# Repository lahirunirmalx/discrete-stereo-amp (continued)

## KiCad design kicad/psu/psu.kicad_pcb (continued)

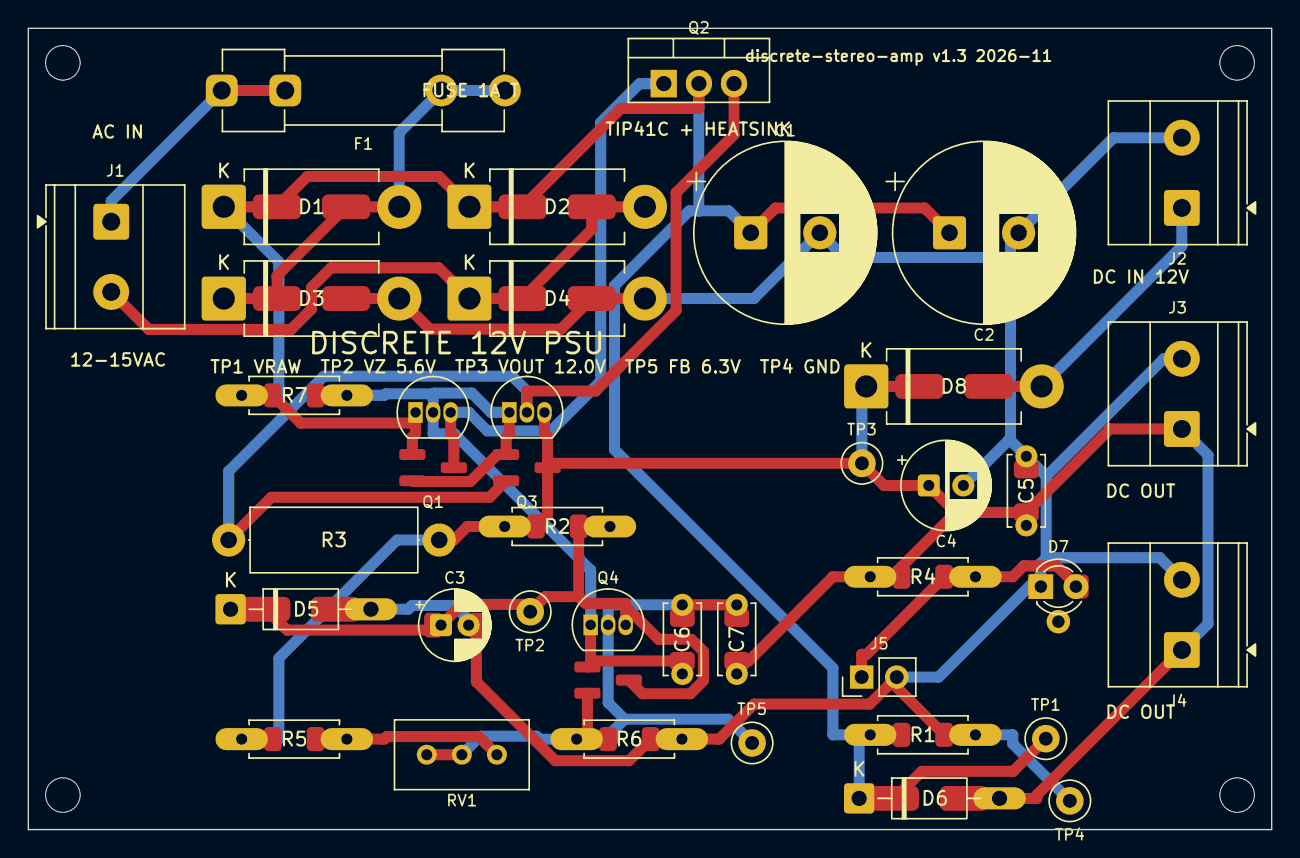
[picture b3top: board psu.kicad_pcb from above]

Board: 2 copper layers, 90.0 x 58.0 mm, 42 parts (0 on the bottom side), 14 nets.

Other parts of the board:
H1, H2, H3, H4: M2.5; Hole_2.5mm

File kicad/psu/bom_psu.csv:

board,qty,refs,value,through_hole,smd_alternative,tolerance_rating,substitutes,matching_note
psu,1,C5,100n,ceramic disc 5 mm,1206,100 nF X7R,100n,
psu,1,C7,100n,ceramic disc 5 mm,1206,"100 nF X7R, 50 V",100n,Feeds fast output steps to the error amplifier.
psu,1,C3,10u,electrolytic 5 mm radial,1206 MLCC,"10 uF, 16 V",4.7u to 47u,Reference filter across the 5.6 V zener.
psu,2,C1 C2,2200u,CP_Radial_D13.0mm_P5.00mm,,"2200 uF, 25 V (35 V if the transformer is 15 VAC)",2200u to 4700u,"Reservoir: raw rail peaks at 21 V no-load from 15 VAC, 23 V at mains +10 percent."
psu,1,C4,220u,CP_Radial_D6.3mm_P2.50mm,,"220 uF, 16 V",100u to 470u,
psu,1,C6,47n,ceramic disc 5 mm,1206,"47 nF X7R or film, 50 V",22n to 100n,"Loop compensation (Q4 collector to base). 22n is faster, 100n slower; all three are stable."
psu,1,D6,1N4007,DO-41,SMA,"1 A, 100 V or more",1N4007 (fitted); 1N4004; UF4007; SMA S1M,Reverse protection of the pass transistor.
psu,4,D1 D2 D3 D4,1N5401,DO-201AD,"SMA (3 A part, e.g. S3M)","3 A, 100 V or more","1N5401 (fitted); 1N5402 / 1N5404 / 1N5408 (same package, higher voltage); SB540 Schottky (less drop, runs cooler); S3M in SMA",All four the same type.
psu,1,D5,5.6V,DO-41,SMA,"5.6 V, 0.5 W, 5 percent",1N5232B (fitted); BZX55C5V6; BZX79C5V6; BZX85C5V6 (1 W); 1N4734A,"Reference. 5.6 V has near-zero tempco and its +2 mV/C cancels Q4's -2 mV/C Vbe; 5.1 V or 6.2 V also work, the trimmer absorbs the difference."
psu,1,D7,LED,3 mm LED (or two small diodes via the middle hole M),1206 LED,"3 mm LED, any colour",any 3 mm or 5 mm LED,"Fit D7 here OR D1 on the volume board, not both."
psu,1,D8,SB540,DO-201AD,"SMA (3 A part, e.g. S3M)","5 A Schottky, 40 V",SB540 (fitted); 1N5822 (3 A); SR540; MBR540; SS54 in SMA,"DC-in path, 0.4 V drop."
psu,1,F1,1.6A T 5x20,Fuseholder_Clip-5x20mm_Littelfuse_100_Inline_P20.50x4.60mm_D1.30mm_Horizontal,,1.6 A slow-blow (T) 5x20 mm + 2 clips,1.6 A T (fitted); 1.25 A T with a 12 VAC transformer; 2 A T only with a larger heatsink on Q2,"On the transformer secondary. Sized for the RMS secondary current (1.5 A at 0.8 A DC), and small enough that the 3.7 A of a clamped short opens it in seconds."
psu,1,J1,AC IN 12-15V,"TerminalBlock_Phoenix_MKDS-1,5-2-5.08_1x02_P5.08mm_Horizontal",,5.08 mm screw terminal,Phoenix MKDS 1.5/2; any 5.08 mm 2-pin block,
psu,1,J2,DC IN 12V,"TerminalBlock_Phoenix_MKDS-1,5-2-5.08_1x02_P5.08mm_Horizontal",,5.08 mm screw terminal,Phoenix MKDS 1.5/2; any 5.08 mm 2-pin block,
psu,1,J3,DC OUT 1,"TerminalBlock_Phoenix_MKDS-1,5-2-5.08_1x02_P5.08mm_Horizontal",,5.08 mm screw terminal,Phoenix MKDS 1.5/2; any 5.08 mm 2-pin block,
psu,1,J4,DC OUT 2,"TerminalBlock_Phoenix_MKDS-1,5-2-5.08_1x02_P5.08mm_Horizontal",,5.08 mm screw terminal,Phoenix MKDS 1.5/2; any 5.08 mm 2-pin block,
psu,1,J5,LED REMOTE,PinHeader_1x02_P2.54mm_Vertical,,"5 percent / 20 percent, standard",,
psu,3,Q1 Q3 Q4,BC547,TO-92,SOT-23 (2-layer board only),hFE 200-450,BC547B/C (fitted); BC548B/C; BC549C or BC550C (lower noise); BC337-25 (800 mA); 2N3904 or PN2222A only turned 180 deg (E-B-C pinout),"Driver (Q1), clamp (Q3) and error amplifier (Q4). No matching."
psu,1,Q2,TIP41C,TO-220-3_Vertical,,"6 A, 100 V, TO-220 on a heatsink","TIP41C (fitted, B-C-E); TIP31C (3 A); BD243C; MJE3055T; TIP41A/B (lower voltage grade is fine at 20 V). All B-C-E: this position has no jumper block",Pass transistor. Dissipates up to 4.9 W: heatsink of 10 C/W or better.
psu,1,R3,0.33 2W,R_Axial_DIN0414_L11.9mm_D4.5mm_P15.24mm_Horizontal,,"0.33 ohm, 3 W, 5 percent",0.33R 2-3 W; 0.47R gives a 1.4 A clamp; 0.22R gives 3 A,Clamp current = 0.65 V / R3.
psu,1,R6,10k,axial 1/4 W,1206,"10k, 1 percent, 1/4 W",10k,Bottom of the output divider. FB = 6.3 V (zener + Vbe) when VOUT is 12.0 V.
psu,1,R2,1k,axial 1/4 W,1206,"1k, 1/4 W, 5 percent",1k,Zener feed from the regulated output: 6 mA.
psu,1,R4,1k,axial 1/4 W,1206,"1k, 1/4 W",470R to 2k2,LED current 10 mA at 1k.
psu,1,R7,2.2k,axial 1/4 W,1206,"2.2k, 0.5 W","2.2k 0.5 W (dissipates 15 mW normally, 0.1 W with the output shorted)",Driver base pull-up from the raw rail; the error amplifier pulls it down.
psu,1,RV1,2k,Potentiometer_Bourns_3296W_Vertical,,"2k trimmer, multi-turn preferred (3296W)",2k 3296W (fitted); 2.2k; 1k (range 11.4 to 12.1 V); 5k with R5 = 6.8k (10.6 to 13.7 V),"Sets VOUT: 11.4 to 12.7 V. Set 12.0 V, or 11.5 V with a 12 VAC transformer."
psu,1,R1,4.7k,axial 1/4 W,1206,"4.7k, 0.5 W",4.7k,Bleeder.
psu,1,R5,8.2k,axial 1/4 W,1206,"8.2k, 1 percent, 1/4 W",8.2k,Top of the output divider (with RV1).
psu,1,TP5,FB 6.3V,TestPoint_Loop_D2.50mm_Drill1.0mm,,"5 percent / 20 percent, standard",,
psu,1,TP4,GND,TestPoint_Loop_D2.50mm_Drill1.0mm,,"5 percent / 20 percent, standard",,
psu,1,TP3,VOUT 12.0V,TestPoint_Loop_D2.50mm_Drill1.0mm,,"5 percent / 20 percent, standard",,
psu,1,TP1,VRAW 14-19V,TestPoint_Loop_D2.50mm_Drill1.0mm,,"5 percent / 20 percent, standard",,
psu,1,TP2,VZ 5.6V,TestPoint_Loop_D2.50mm_Drill1.0mm,,"5 percent / 20 percent, standard",,

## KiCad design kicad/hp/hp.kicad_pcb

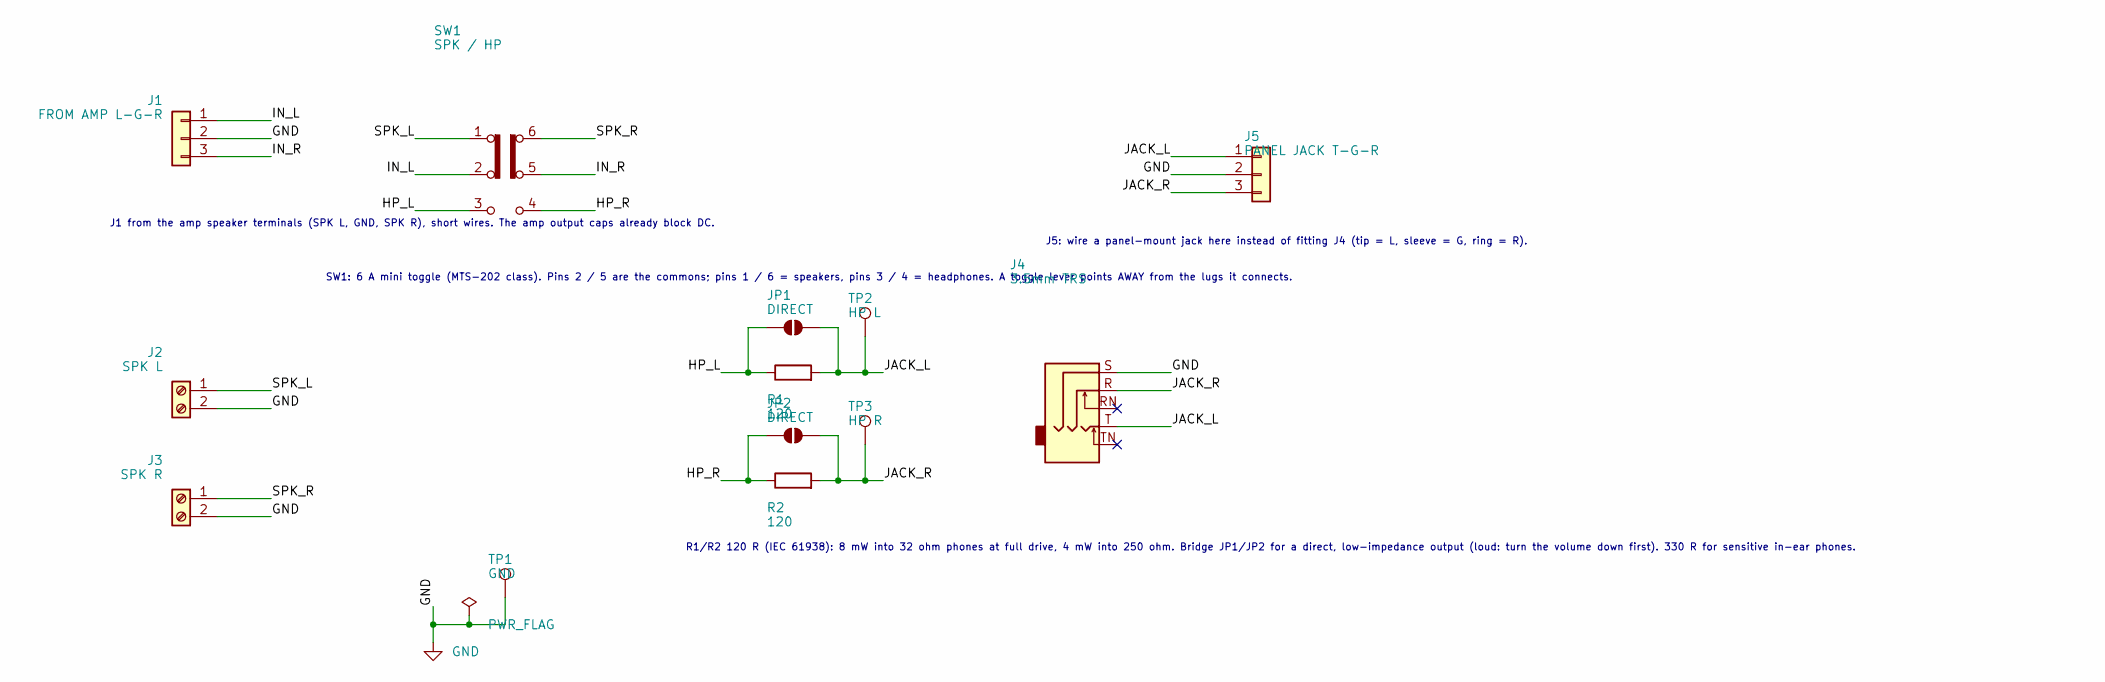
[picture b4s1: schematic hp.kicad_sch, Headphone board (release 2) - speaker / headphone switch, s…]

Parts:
J1: FROM AMP L-G-R; PinHeader_1x03_P2.54mm_Vertical
J2: SPK L; TerminalBlock_Phoenix_MKDS-1,5-2-5.08_1x02_P5.08mm_Horizont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
J3: SPK R; TerminalBlock_Phoenix_MKDS-1,5-2-5.08_1x02_P5.08mm_Horizont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
J4: 3.5mm TRS; Jack_3.5mm_CUI_SJ1-3535NG_Horizontal
J5: PANEL JACK T-G-R; PinHeader_1x03_P2.54mm_Vertical
JP1, JP2: DIRECT; SolderJumper-2_P1.3mm_Open_Pad1.0x1.5mm
R1, R2: 120; R_Axial_1206
SW1: SPK / HP; SW_DPDT_MTS202
TP1: GND; TestPoint_Loop_D2.50mm_Drill1.0mm
TP2: HP L; TestPoint_Loop_D2.50mm_Drill1.0mm
TP3: HP R; TestPoint_Loop_D2.50mm_Drill1.0mm

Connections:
/HP_L: JP1.1 (A), R1.1, R1.1S, SW1.3 (C)
/HP_R: JP2.1 (A), R2.1, R2.1S, SW1.4 (A)
/IN_L: J1.1, SW1.2 (B)
/IN_R: J1.3, SW1.5 (B)
/JACK_L: J4.T, J5.1, JP1.2 (B), R1.2, R1.2S, TP2.1
/JACK_R: J4.R, J5.3, JP2.2 (B), R2.2, R2.2S, TP3.1
/SPK_L: J2.1, SW1.1 (A)
/SPK_R: J3.1, SW1.6 (C)
GND: J1.2, J2.2, J3.2, J4.S, J5.2, TP1.1

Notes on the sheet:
J1 from the amp speaker terminals (SPK L, GND, SPK R), short wires. The amp output caps already block DC.
SW1: 6 A mini toggle (MTS-202 class). Pins 2 / 5 are the commons; pins 1 / 6 = speakers, pins 3 / 4 = headphones. A toggle lever points AWAY from the lugs it connects.
R1/R2 120 R (IEC 61938): 8 mW into 32 ohm phones at full drive, 4 mW into 250 ohm. Bridge JP1/JP2 for a direct, low-impedance output (loud: turn the volume down first). 330 R for sensitive in-ear phones.
J5: wire a panel-mount jack here instead of fitting J4 (tip = L, sleeve = G, ring = R).

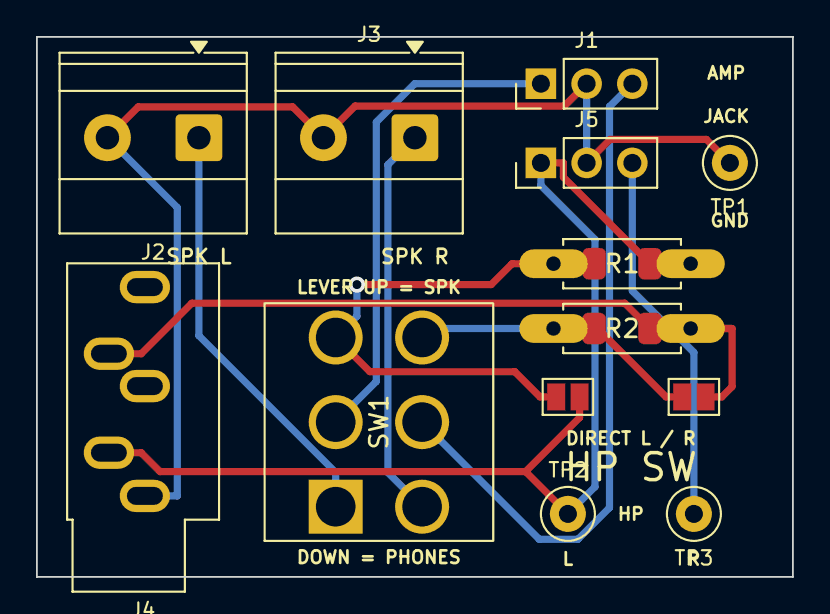
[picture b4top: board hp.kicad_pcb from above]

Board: 2 copper layers, 42.0 x 30.0 mm, 13 parts (0 on the bottom side), 9 nets.

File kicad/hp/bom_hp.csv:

board,qty,refs,value,through_hole,smd_alternative,tolerance_rating,substitutes,matching_note
hp,1,J4,3.5mm TRS,Jack_3.5mm_CUI_SJ1-3535NG_Horizontal,,"3.5 mm TRS jack, through-hole, CUI SJ1-3535NG pattern",SJ1-3535NG (fitted); SJ1-3535N; SJ1-3525N (same T/R/S pins); or any panel-mount jack wired to J5,"Only T, R and S are used; the switch pins TN / RN stay open."
hp,1,J1,FROM AMP L-G-R,PinHeader_1x03_P2.54mm_Vertical,,2.54 mm header or 5.08 mm screw terminal,,
hp,1,J5,PANEL JACK T-G-R,PinHeader_1x03_P2.54mm_Vertical,,2.54 mm header or 5.08 mm screw terminal,,
hp,1,J2,SPK L,"TerminalBlock_Phoenix_MKDS-1,5-2-5.08_1x02_P5.08mm_Horizontal",,2.54 mm header or 5.08 mm screw terminal,,
hp,1,J3,SPK R,"TerminalBlock_Phoenix_MKDS-1,5-2-5.08_1x02_P5.08mm_Horizontal",,2.54 mm header or 5.08 mm screw terminal,,
hp,2,R1 R2,120,axial 1/4 W,1206,"120 ohm, 1 percent, 1/4 W","120R (IEC 61938, fitted); 33R to 68R for a louder low-impedance drive; 330R for sensitive in-ear phones; 0R or bridge JP1/JP2 for direct drive",Same value for both channels. 8 mW into 32 ohm at full drive with 120 R.
hp,1,SW1,SPK / HP,"DPDT mini toggle, 2 x 3 lugs 4.7 x 4.8 mm",,"DPDT on-on miniature toggle, 2 A or more, lugs 4.7 x 4.8 mm",MTS-202 (fitted); any DPDT mini toggle with the same lug pattern; a panel DPDT on six wires; a 2 A DPDT slide switch on wires,"Carries the speaker current (0.9 A peak), so no sub-miniature signal switches. Commons on pads 2 / 5, speakers on 1 / 6, headphones on 3 / 4; a toggle lever points away from the lugs it connects."
hp,1,TP1,GND,TestPoint_Loop_D2.50mm_Drill1.0mm,,"5 percent / 20 percent, standard",,
hp,1,TP2,HP L,TestPoint_Loop_D2.50mm_Drill1.0mm,,"5 percent / 20 percent, standard",,
hp,1,TP3,HP R,TestPoint_Loop_D2.50mm_Drill1.0mm,,"5 percent / 20 percent, standard",,

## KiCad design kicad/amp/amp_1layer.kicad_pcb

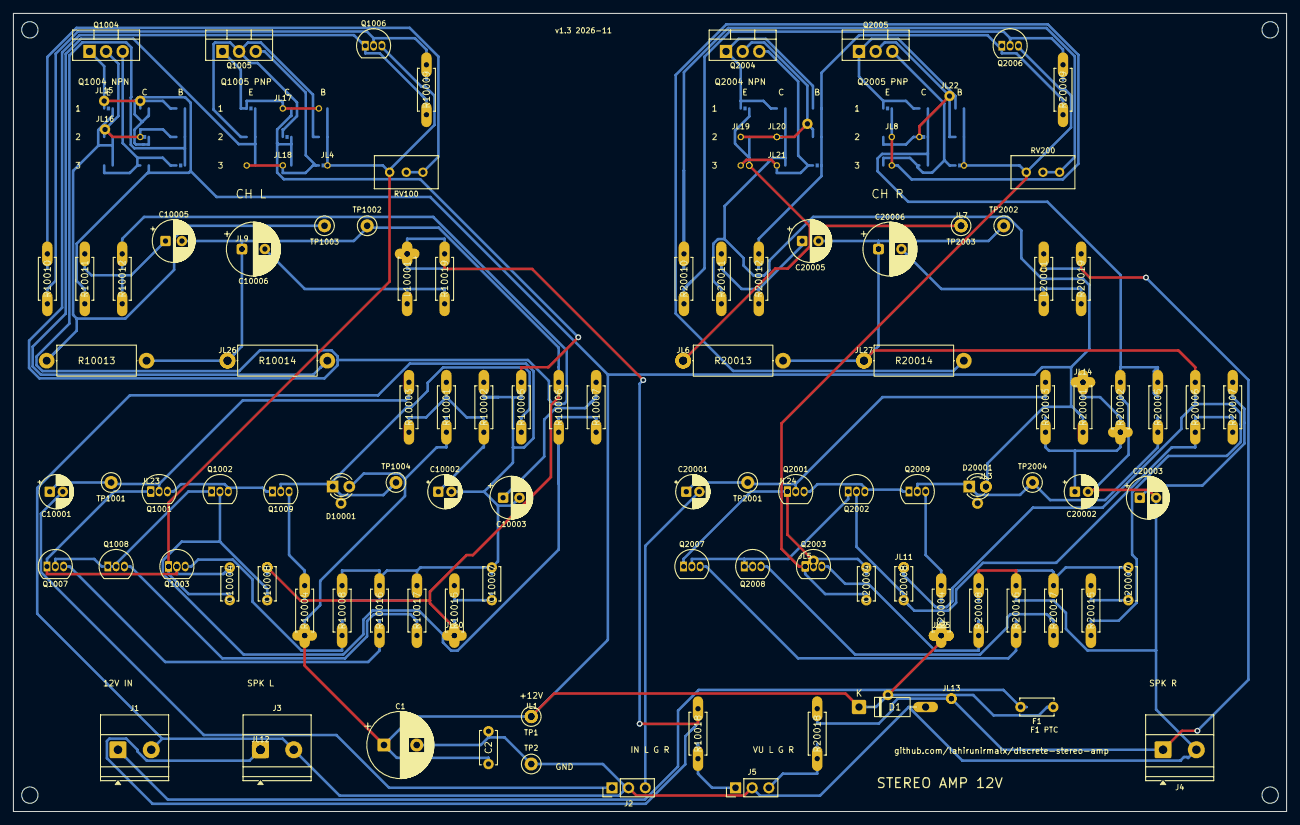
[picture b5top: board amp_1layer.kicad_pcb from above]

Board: 2 copper layers, 194.3 x 121.8 mm, 164 parts (0 on the bottom side), 65 nets.

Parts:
C1: 1000u 25V; CP_Radial_D10.0mm_P5.00mm
C2, C10007, C20007: 100n; C_P5_1206
C10001, C20001: 2.2u; CE_P2_1206
C10002, C20002: 47u; CE_P2_1206
C10003, C20003: 220u; CP_Radial_D6.3mm_P2.50mm
C10004, C20004: 220p; C_P5_1206
C10005, C20005: 100u; CP_Radial_D6.3mm_P2.50mm
C10006, C20006: 1000u; CP_Radial_D8.0mm_P3.50mm
C10008, C20008: 47p; C_P5_1206
D1: 1N4007; D_DO41_SMA
D10001, D20001: LED red; LED_D3_1206
F1: PTC 1.1A; C_P5_1206
H1, H2, H3, H4: M2.5; Hole_2.5mm
J1: DC 12V IN; TerminalBlock_Phoenix_MKDS-1,5-2-5.08_1x02_P5.08mm_Horizont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
J2: IN L-G-R; PinHeader_1x03_P2.54mm_Vertical
J3: SPK L; TerminalBlock_Phoenix_MKDS-1,5-2-5.08_1x02_P5.08mm_Horizont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
J4: SPK R; TerminalBlock_Phoenix_MKDS-1,5-2-5.08_1x02_P5.08mm_Horizont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
J5: VU L-G-R; PinHeader_1x03_P2.54mm_Vertical
JL1, JL2, JL3, JL4, JL5, JL6, JL7, JL8, JL9, JL10, JL11, JL12, JL13, JL14, JL15, JL16, JL17, JL18, JL19, JL20, JL21, JL22, JL23, JL24, JL25, JL26, JL27: wire link; WireLink
JP10001, JP20001: E>E4; SolderJumper-2_P1.3mm_Bridged_Pad1.0x1.5mm
JP10002, JP20002: E>+12V; SolderJumper-2_P1.3mm_Open_Pad1.0x1.5mm
JP10003, JP20003: E>VAS; SolderJumper-2_P1.3mm_Open_Pad1.0x1.5mm
JP10004, JP20004: C>E4; SolderJumper-2_P1.3mm_Open_Pad1.0x1.5mm
JP10005, JP20005: C>+12V; SolderJumper-2_P1.3mm_Bridged_Pad1.0x1.5mm
JP10006, JP20006: C>VAS; SolderJumper-2_P1.3mm_Open_Pad1.0x1.5mm
JP10007, JP20007: B>E4; SolderJumper-2_P1.3mm_Open_Pad1.0x1.5mm
JP10008, JP20008: B>+12V; SolderJumper-2_P1.3mm_Open_Pad1.0x1.5mm
JP10009, JP20009: B>VAS; SolderJumper-2_P1.3mm_Bridged_Pad1.0x1.5mm
JP10011, JP20011: C>E5; SolderJumper-2_P1.3mm_Open_Pad1.0x1.5mm
JP10012, JP20012: C>GND; SolderJumper-2_P1.3mm_Bridged_Pad1.0x1.5mm
JP10013, JP20013: C>B5; SolderJumper-2_P1.3mm_Open_Pad1.0x1.5mm
JP10014, JP20014: E>E5; SolderJumper-2_P1.3mm_Bridged_Pad1.0x1.5mm
JP10015, JP20015: E>GND; SolderJumper-2_P1.3mm_Open_Pad1.0x1.5mm
JP10016, JP20016: E>B5; SolderJumper-2_P1.3mm_Open_Pad1.0x1.5mm
JP10017, JP20017: B>E5; SolderJumper-2_P1.3mm_Open_Pad1.0x1.5mm
JP10018, JP20018: B>GND; SolderJumper-2_P1.3mm_Open_Pad1.0x1.5mm
JP10019, JP20019: B>B5; SolderJumper-2_P1.3mm_Bridged_Pad1.0x1.5mm
L10001, L20001: 2.2uH 1A; R_Axial_1206
Q1001, Q1002, Q1009, Q2001, Q2002, Q2009: BC557; TO92_SOT23
Q1003, Q1006, Q1007, Q1008, Q2003, Q2006, Q2007, Q2008: BC547; TO92_SOT23
Q1004, Q2004: BD139; TO-220-3_Vertical
Q1005, Q2005: BD140; TO-220-3_Vertical
R10001, R10002, R10003, R20001, R20002, R20003: 47k; R_Axial_1206
R10004, R20004: 1.2k; R_Axial_1206
R10005, R20005: 4.7k; R_Axial_1206
R10006, R20006: 22k; R_Axial_1206
R10007, R10018, R20007, R20018: 1k; R_Axial_1206
R10008, R20008: 47; R_Axial_1206
R10009, R10010, R20009, R20010: 750; R_Axial_1206
R10011, R10012, R20011, R20012: 270; R_Axial_1206
R10013, R10014, R20013, R20014: 0.47; R_Axial_DIN0414_L11.9mm_D4.5mm_P15.24mm_Horizontal
R10015, R10019, R20015, R20019: 10; R_Axial_1206
R10016, R10017, R20016, R20017: 100; R_Axial_1206
RV100, RV200: 500; Potentiometer_Bourns_3296W_Vertical
TP1: +12V; TestPoint_Loop_D2.50mm_Drill1.0mm
TP2: GND; TestPoint_Loop_D2.50mm_Drill1.0mm
TP1001, TP2001: B1 6.1V; TestPoint_Loop_D2.50mm_Drill1.0mm
TP1002, TP2002: OUT 5.9V; TestPoint_Loop_D2.50mm_Drill1.0mm
TP1003, TP2003: E4 bias; TestPoint_Loop_D2.50mm_Drill1.0mm
TP1004, TP2004: LED 10.2V; TestPoint_Loop_D2.50mm_Drill1.0mm

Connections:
+12V: C1.1, C2.1, C2.1S, D1.1, D1.1S, D10001.2, D10001.2S, D20001.2, D20001.2S, F1.2, F1.2S, JL1.1, JL1.2, JL2.1, JL2.2, JL3.1, JL3.2, JL25.1, JL25.2, JP10002.2, JP10005.2, JP10008.2, JP20002.2, JP20005.2, JP20008.2, R10001.1, R10001.1S, R10004.1, R10004.1S, R10011.1, R10011.1S, R20001.1, R20001.1S, R20004.1, R20004.1S, R20011.1, R20011.1S, TP1.1
/B5_L: C10004.1, C10004.1S, JL4.1, JL4.2, JP10013.2, JP10016.2, JP10019.2, Q1003.1, Q1006.3, RV100.3
/B5_R: C20004.1, C20004.1S, JL5.1, JL5.2, JP20013.2, JP20016.2, JP20019.2, Q2003.1, Q2006.3, RV200.3
/E4_L: JP10001.2, JP10004.2, JP10007.2, R10013.1, TP1003.1
/E4_R: JL6.1, JL6.2, JL7.1, JL7.2, JP20001.2, JP20004.2, JP20007.2, R20013.1, TP2003.1
/E5_L: JP10011.2, JP10014.2, JP10017.2, R10014.2
/E5_R: JL8.1, JL8.2, JP20011.2, JP20014.2, JP20017.2, R20014.2
/IN_L: C10001.2, C10001.2S, J2.1
/IN_R: C20001.2, C20001.2S, J2.3
/OUT_L: C10005.2, C10006.1, C10008.2, C10008.2S, JL9.1, JL9.2, JL10.1, JL10.2, JL26.1, JL26.2, R10006.2, R10006.2S, R10013.2, R10014.1, R10015.1, R10015.1S, TP1002.1
/OUT_R: C20005.2, C20006.1, C20008.2, C20008.2S, JL11.1, JL11.2, JL27.1, JL27.2, R20006.2, R20006.2S, R20013.2, R20014.1, R20015.1, R20015.1S, TP2002.1
/SPK_L: J3.1, JL12.1, JL12.2, L10001.2, L10001.2S, R10018.1, R10018.1S, R10019.2, R10019.2S
/SPK_R: J4.1, JL13.1, JL13.2, L20001.2, L20001.2S, R20018.1, R20018.1S, R20019.2, R20019.2S
/VAS_L: JP10003.2, JP10006.2, JP10009.2, Q1006.1, R10009.1, R10009.1S, R10012.2, R10012.2S
/VAS_R: JP20003.2, JP20006.2, JP20009.2, Q2006.1, R20009.1, R20009.1S, R20012.2, R20012.2S
/VIN: F1.1, F1.1S, J1.1
/VU_L: J5.1, R10018.2, R10018.2S
/VU_R: J5.3, R20018.2, R20018.2S
GND: C1.2, C2.2, C2.2S, C10002.2, C10002.2S, C10003.2, C10007.2, C10007.2S, C20002.2, C20002.2S, C20003.2, C20007.2, C20007.2S, D1.2, D1.2S, J1.2, J2.2, J3.2, J4.2, J5.2, JP10012.2, JP10015.2, JP10018.2, JP20012.2, JP20015.2, JP20018.2, R10002.2, R10002.2S, R10005.2, R10005.2S, R10008.2, R10008.2S, R10016.2, R10016.2S, R10017.2, R10017.2S, R20002.2, R20002.2S, R20005.2, R20005.2S, R20008.2, R20008.2S, R20016.2, R20016.2S, R20017.2, R20017.2S, TP2.1
unnamed: C10002.1, C10002.1S, R10001.2, R10001.2S, R10002.1, R10002.1S, R10003.1, R10003.1S
unnamed: C10003.1, R10007.2, R10007.2S
unnamed: C10005.1, R10011.2, R10011.2S, R10012.1, R10012.1S
unnamed: C10006.2, L10001.1, L10001.1S, R10019.1, R10019.1S
unnamed: C10007.1, C10007.1S, R10015.2, R10015.2S
unnamed: C20002.1, C20002.1S, JL14.1, JL14.2, R20001.2, R20001.2S, R20002.1, R20002.1S, R20003.1, R20003.1S
unnamed: C20003.1, R20007.2, R20007.2S
unnamed: C20005.1, R20011.2, R20011.2S, R20012.1, R20012.1S
unnamed: C20006.2, L20001.1, L20001.1S, R20019.1, R20019.1S
unnamed: C20007.1, C20007.1S, R20015.2, R20015.2S
unnamed: D10001.1, D10001.1S, Q1009.2, R10005.1, R10005.1S, TP1004.1
unnamed: D20001.1, D20001.1S, Q2009.2, R20005.1, R20005.1S, TP2004.1
unnamed: JL15.1, JL15.2, JP10001.1, JP10002.1, JP10003.1, Q1004.1
unnamed: JL16.1, JL16.2, JP10004.1, JP10005.1, JP10006.1, Q1004.2
unnamed: JP10007.1, JP10008.1, JP10009.1, Q1004.3
unnamed: JP10011.1, JP10012.1, JP10013.1, Q1005.2
unnamed: JL17.1, JL17.2, JP10014.1, JP10015.1, JP10016.1, Q1005.1
unnamed: JL18.1, JL18.2, JP10017.1, JP10018.1, JP10019.1, Q1005.3
unnamed: JP20001.1, JP20002.1, JP20003.1, Q2004.1
unnamed: JL19.1, JL19.2, JL20.1, JL20.2, JP20004.1, JP20005.1, JP20006.1, Q2004.2
unnamed: JL21.1, JL21.2, JP20007.1, JP20008.1, JP20009.1, Q2004.3
unnamed: JL22.1, JL22.2, JP20011.1, JP20012.1, JP20013.1, Q2005.2
unnamed: JP20014.1, JP20015.1, JP20016.1, Q2005.1
unnamed: JP20017.1, JP20018.1, JP20019.1, Q2005.3
unnamed: C10001.1, C10001.1S, Q1001.2, R10003.2, R10003.2S, TP1001.1
unnamed: C10004.2, C10004.2S, JL23.1, JL23.2, Q1001.1, Q1003.2, Q1007.1
unnamed: Q1001.3, Q1002.3, Q1009.1
unnamed: C10008.1, C10008.1S, Q1002.2, R10006.1, R10006.1S, R10007.1, R10007.1S
unnamed: Q1002.1, Q1007.2, Q1008.1, Q1008.2
unnamed: Q1003.3, R10008.1, R10008.1S
unnamed: Q1006.2, R10009.2, R10009.2S, R10010.1, R10010.1S
unnamed: Q1007.3, R10016.1, R10016.1S
unnamed: Q1008.3, R10017.1, R10017.1S
unnamed: Q1009.3, R10004.2, R10004.2S
unnamed: C20001.1, C20001.1S, Q2001.2, R20003.2, R20003.2S, TP2001.1
unnamed: C20004.2, C20004.2S, JL24.1, JL24.2, Q2001.1, Q2003.2, Q2007.1
unnamed: Q2001.3, Q2002.3, Q2009.1
unnamed: C20008.1, C20008.1S, Q2002.2, R20006.1, R20006.1S, R20007.1, R20007.1S
unnamed: Q2002.1, Q2007.2, Q2008.1, Q2008.2
unnamed: Q2003.3, R20008.1, R20008.1S
unnamed: Q2006.2, R20009.2, R20009.2S, R20010.1, R20010.1S
unnamed: Q2007.3, R20016.1, R20016.1S
unnamed: Q2008.3, R20017.1, R20017.1S
unnamed: Q2009.3, R20004.2, R20004.2S
unnamed: R10010.2, R10010.2S, RV100.1, RV100.2
unnamed: R20010.2, R20010.2S, RV200.1, RV200.2
